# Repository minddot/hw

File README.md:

# MindDot Hardware

## Components

- ESP32-C3-WROOM-02
- AHT10
- LIS2DH12
- HX6306P332MR

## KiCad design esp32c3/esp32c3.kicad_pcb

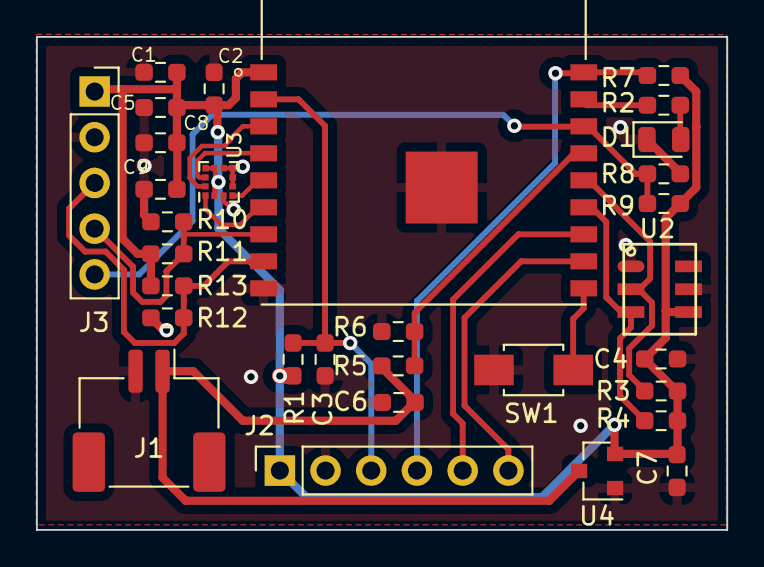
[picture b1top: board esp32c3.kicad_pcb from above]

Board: 2 copper layers, 38.4 x 27.4 mm, 31 parts (0 on the bottom side), 20 nets.

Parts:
C1, C3, C5: 10uF; R_0603_1608Metric_Pad0.98x0.95mm_HandSolder
C2, C8, C9: 0.1uF; R_0603_1608Metric_Pad0.98x0.95mm_HandSolder
C4: 100nF; R_0603_1608Metric_Pad0.98x0.95mm_HandSolder
C6, C7: 1uF; R_0603_1608Metric_Pad0.98x0.95mm_HandSolder
D1: LED_RED; LED_0805_2012Metric
J1: A1501WR-S-2P; JST_ZE_BM02B-ZESS-TBT_1x02-1MP_P1.50mm_Vertical
J2: Conn_01x06; PinSocket_1x06_P2.54mm_Vertical
J3: Conn_01x05; PinSocket_1x05_P2.54mm_Vertical
R1: 12k; R_0603_1608Metric_Pad0.98x0.95mm_HandSolder
R2, R3, R4: 10k; R_0603_1608Metric_Pad0.98x0.95mm_HandSolder
R5, R8, R9, R10, R11, R12, R13: 100k; R_0603_1608Metric_Pad0.98x0.95mm_HandSolder
R6: 200k; R_0603_1608Metric_Pad0.98x0.95mm_HandSolder
R7: 5.1k; R_0603_1608Metric_Pad0.98x0.95mm_HandSolder
SW1: wake up; SW-SMD_2PIN-L4.05-W3.00-L
U1: ESP32-C3-WROOM-02
U2: AHT10
U3: LIS2DH; LGA-12_2x2mm_P0.5mm
U4: HX6306; SOT-23

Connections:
3.3V: C1.1, C2.1, C4.1, C5.1, C7.1, C8.1, C9.1, J2.1, J3.1, R1.1, R3.1, R4.1, R7.2, R9.2, R11.2, R13.2, U1.1 (3V3), U2.4 (VDD), U3.2 (~CS), U3.9 (Vdd), U3.10 (Vdd_IO), U4.2 (VOUT)
ADC: R5.2, R6.1, U1.15 (IO3)
EN: C3.1, J2.3, R1.2, U1.2 (EN)
GND: C1.2, C2.2, C3.2, C4.2, C5.2, C6.2, C7.2, C8.2, C9.2, D1.1 (K), J1.2, J2.2, J3.2, R6.2, R8.2, R10.2, R12.2, SW1.1, U1.9 (GND), U1.19 (GND), U2.1 (ADR), U2.5 (GND), U3.3 (SA0/SDO), U3.5 (RES), U3.6 (GND), U3.7 (GND), U3.8 (GND), U4.1 (GND)
INT: SW1.2, U1.10 (IO10)
INT1: U1.3 (IO4), U3.12 (INT1)
INT2: U1.4 (IO5), U3.11 (INT2)
IO0: J2.4, R7.1, U1.18 (IO0)
IO2: J3.5, R8.1, R9.1, U1.16 (IO2)
IO8: J3.4, R10.1, R11.1, U1.7 (IO8)
IO9: J3.3, R12.1, R13.1, U1.8 (IO9)
LED: R2.1, U1.17 (IO1)
unnamed: D1.2 (A), R2.2
RXD: J2.6, U1.11 (RXD)
SCL: U1.6 (IO7), U3.1 (SCL/SPC)
SCL_AHT10: R4.2, U1.13 (IO18), U2.3 (SCL)
SDA: U1.5 (IO6), U3.4 (SDA/SDI)
SDA_AHT10: R3.2, U1.14 (IO19), U2.2 (SDA)
TXD: J2.5, U1.12 (TXD)
V_In: C6.1, J1.1, R5.1, U4.3 (VIN)

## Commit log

2021-09-14 add datasheets for MCP and ESP32
2021-09-14 add sensor datasheets
2021-09-14 add additional SoCs for ESP32
2021-09-14 alternative LDO datasheet
2021-09-15 Add HX630 LDO
2021-11-29 Add Components
    Add BOM close #4
2021-12-08 finish schematic
2021-12-13 add wake up, voltage measurement
2022-01-03 finish first version of PCB
2022-01-06 Place components on one side
2022-04-21 add LIS2DH12 datasheet
2022-04-21 update readme for accelerometer component
2022-04-22 Complete LIS2DH12 modification
2022-04-22 ignore backup folder
2022-04-22 remove backup folder
2022-04-22 prepare v2.0-alpha-1 for fabrication
2022-04-22 ignore ds_store files
